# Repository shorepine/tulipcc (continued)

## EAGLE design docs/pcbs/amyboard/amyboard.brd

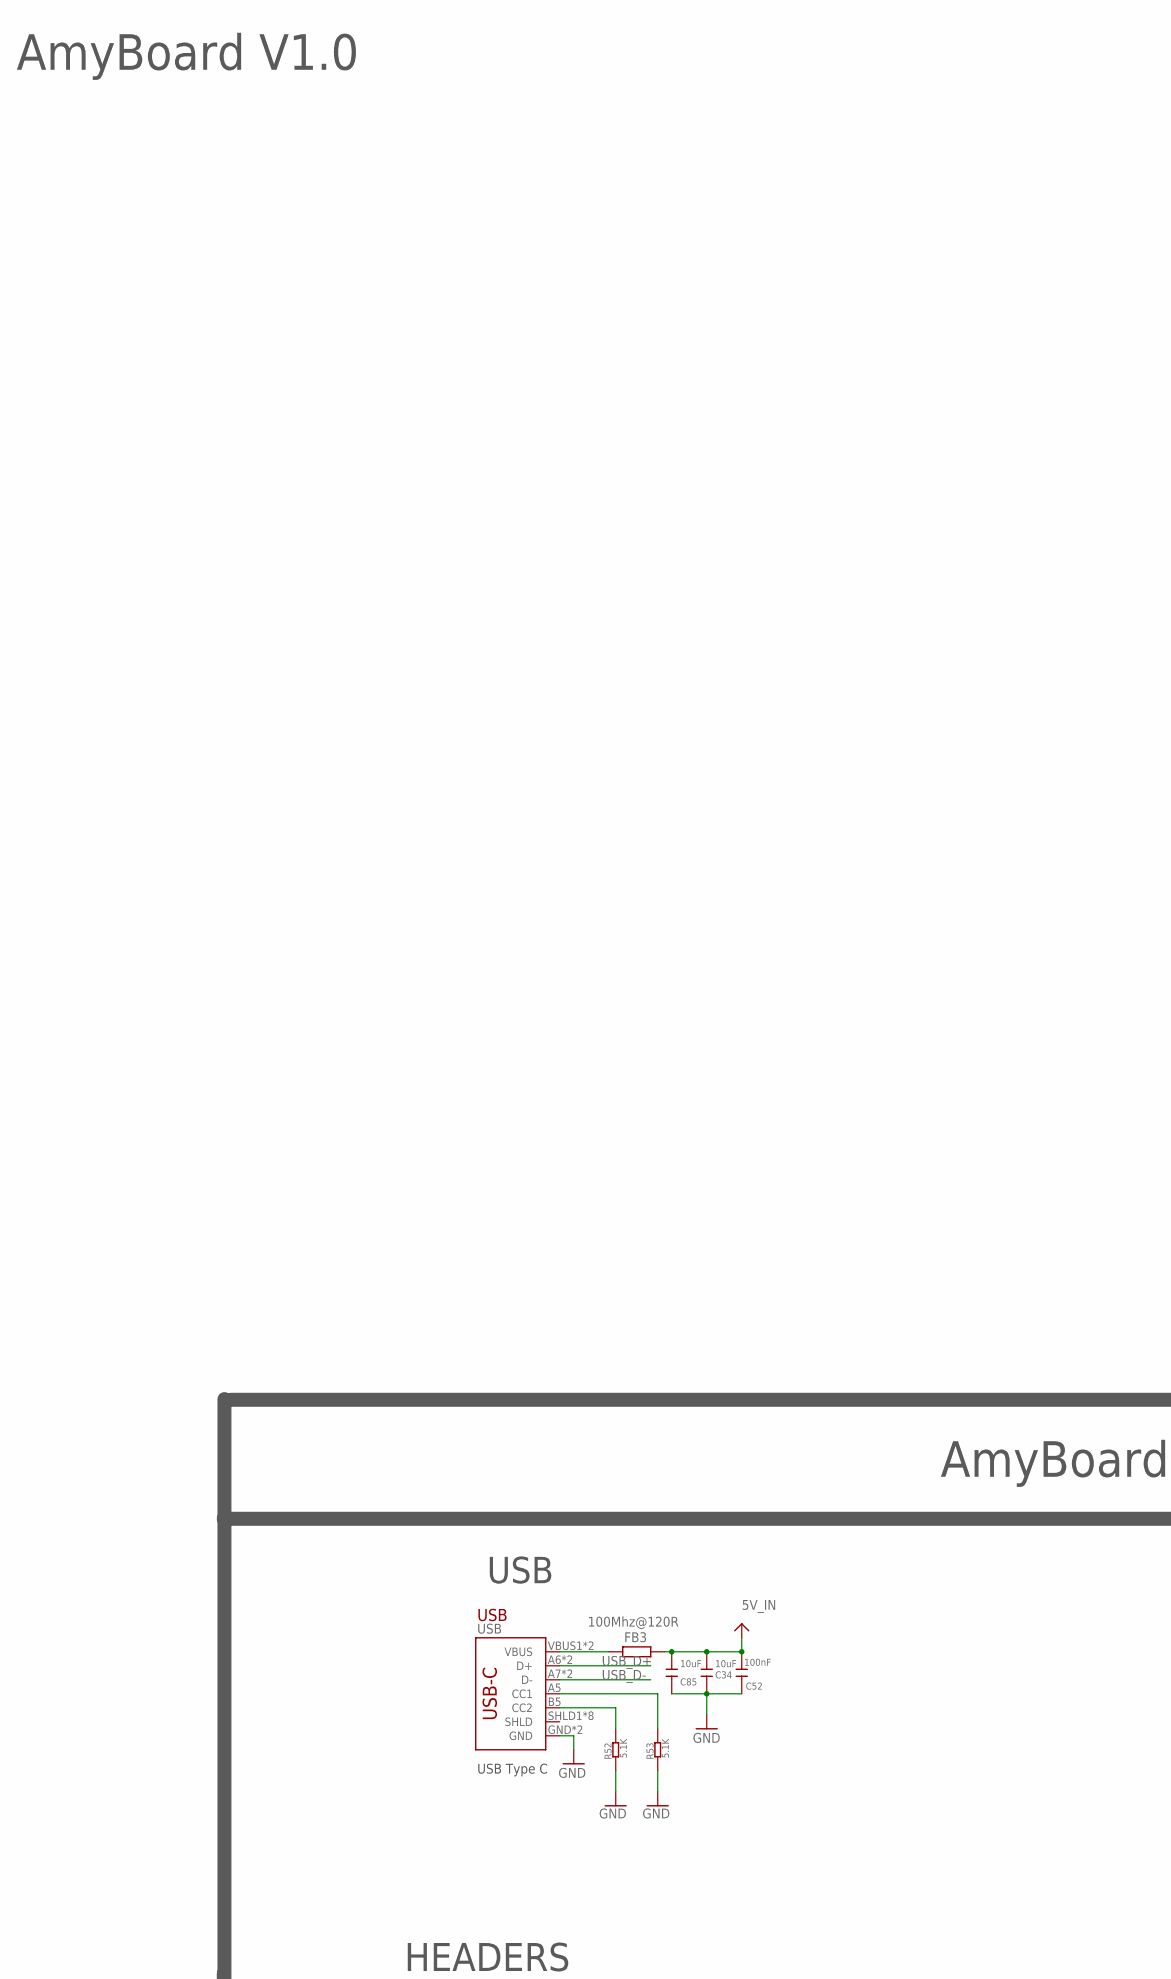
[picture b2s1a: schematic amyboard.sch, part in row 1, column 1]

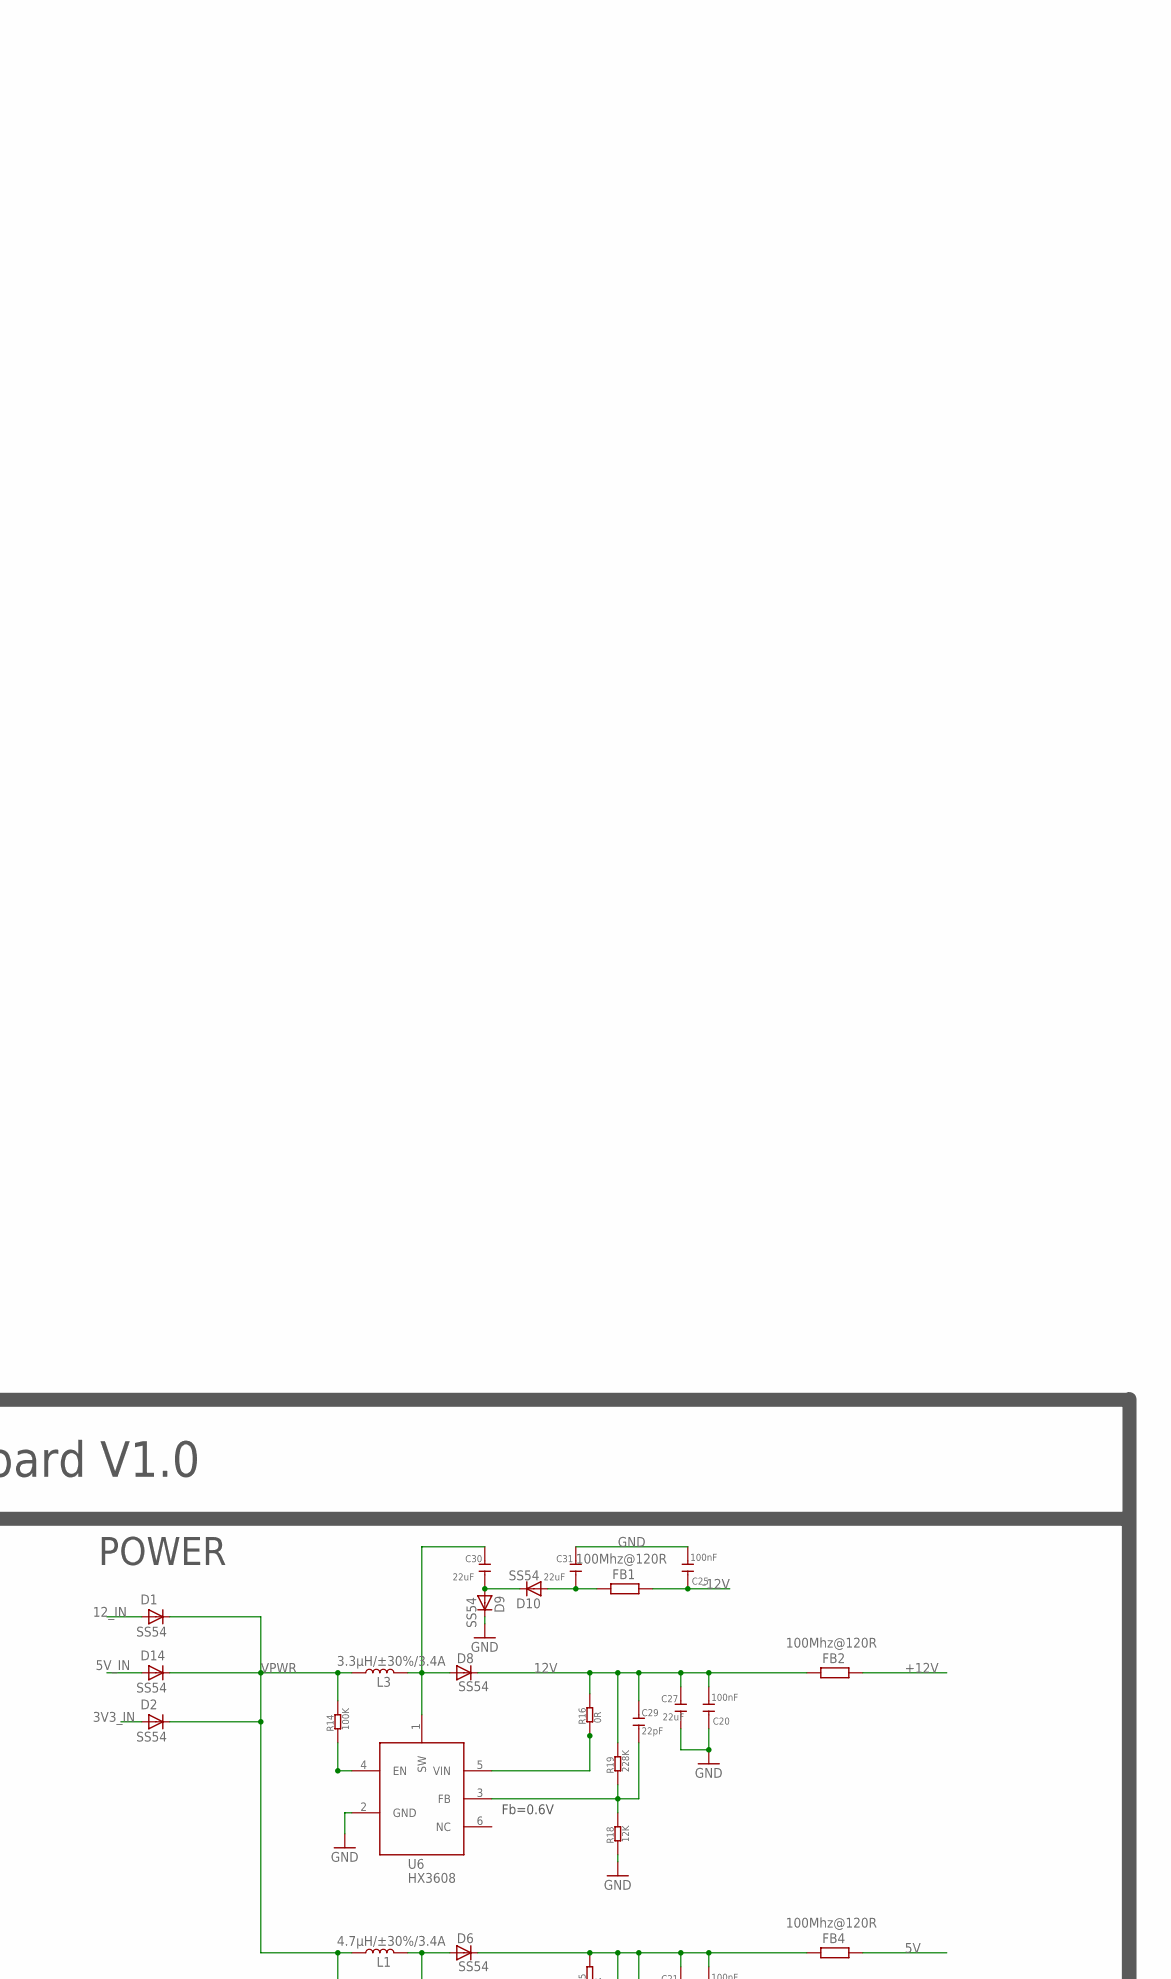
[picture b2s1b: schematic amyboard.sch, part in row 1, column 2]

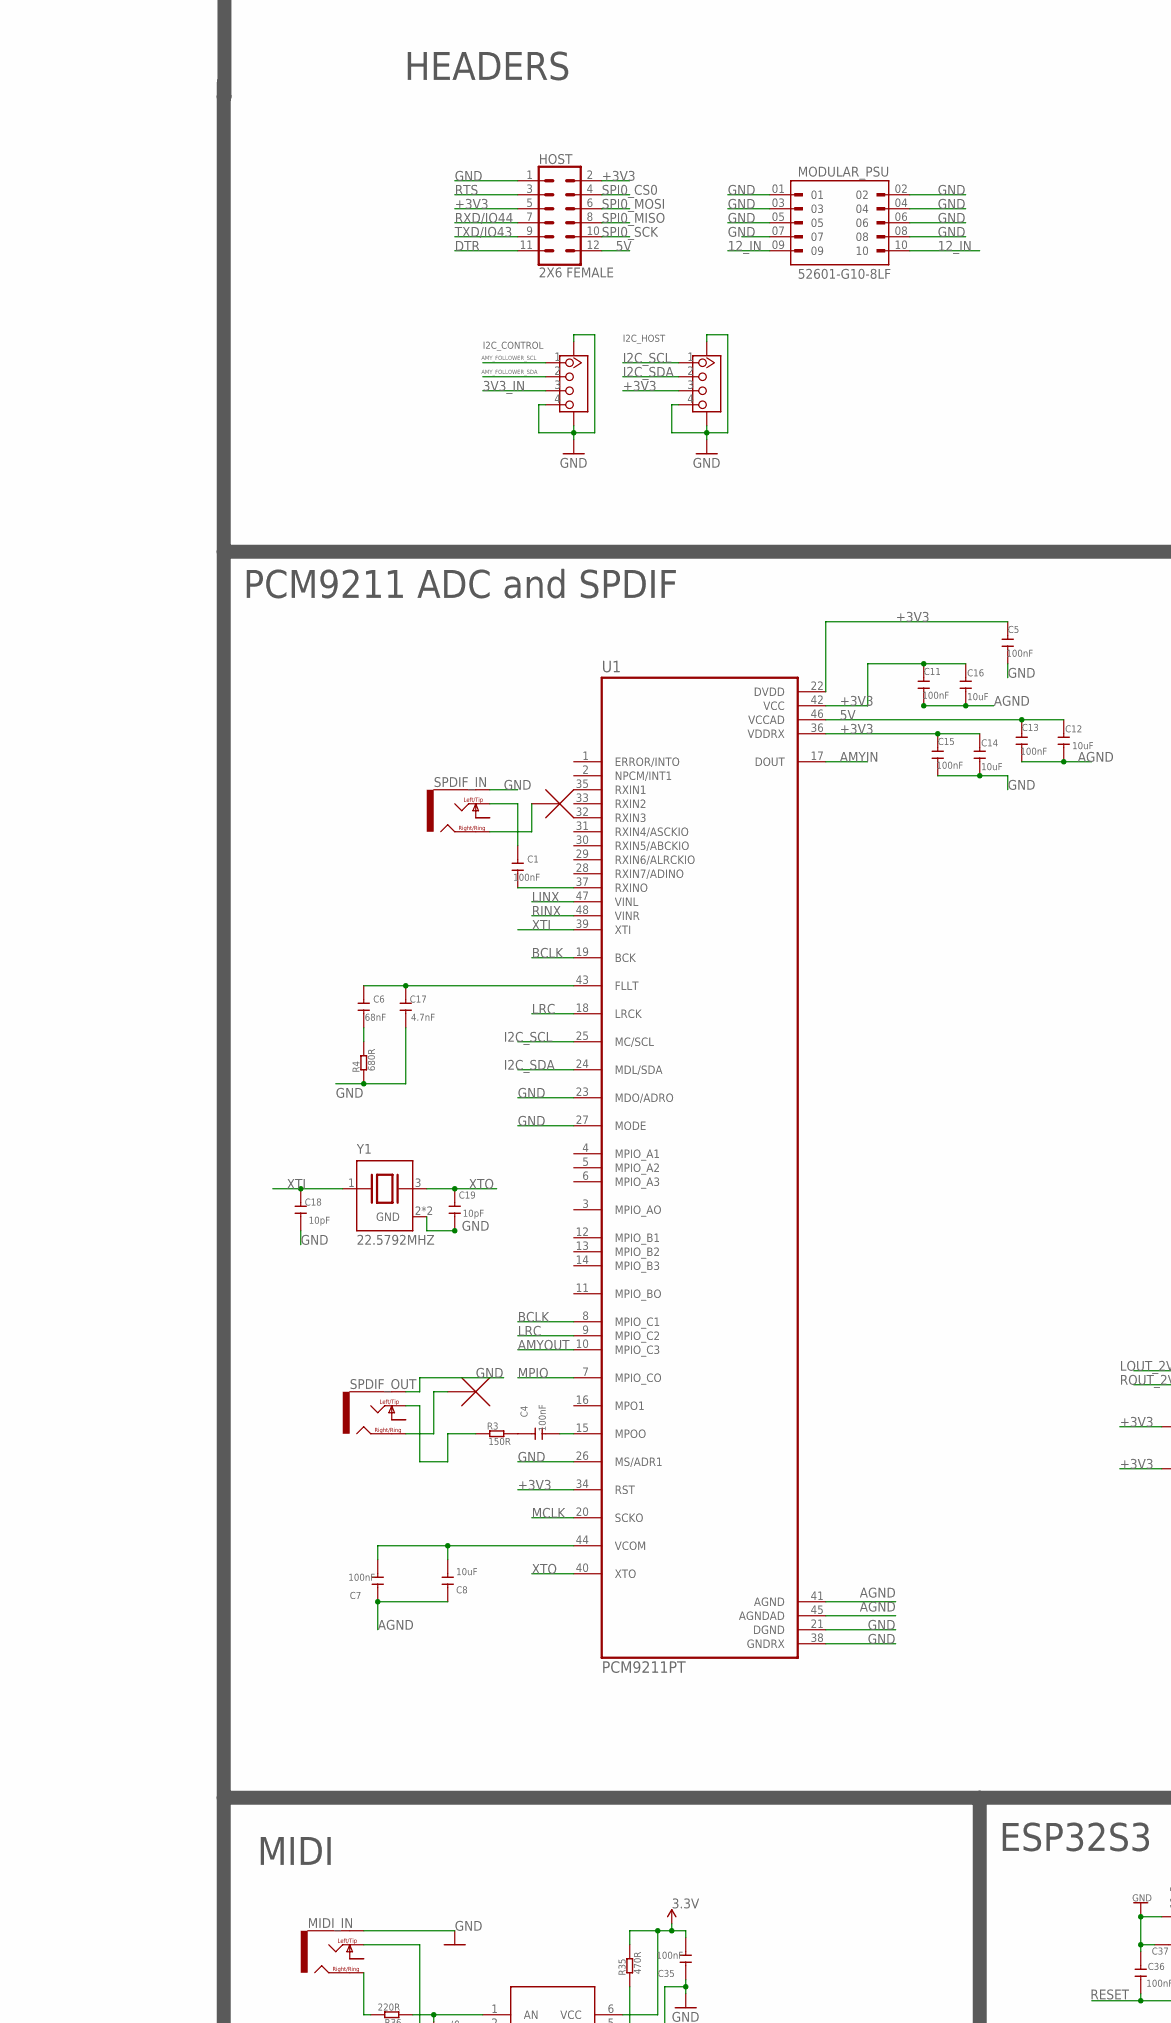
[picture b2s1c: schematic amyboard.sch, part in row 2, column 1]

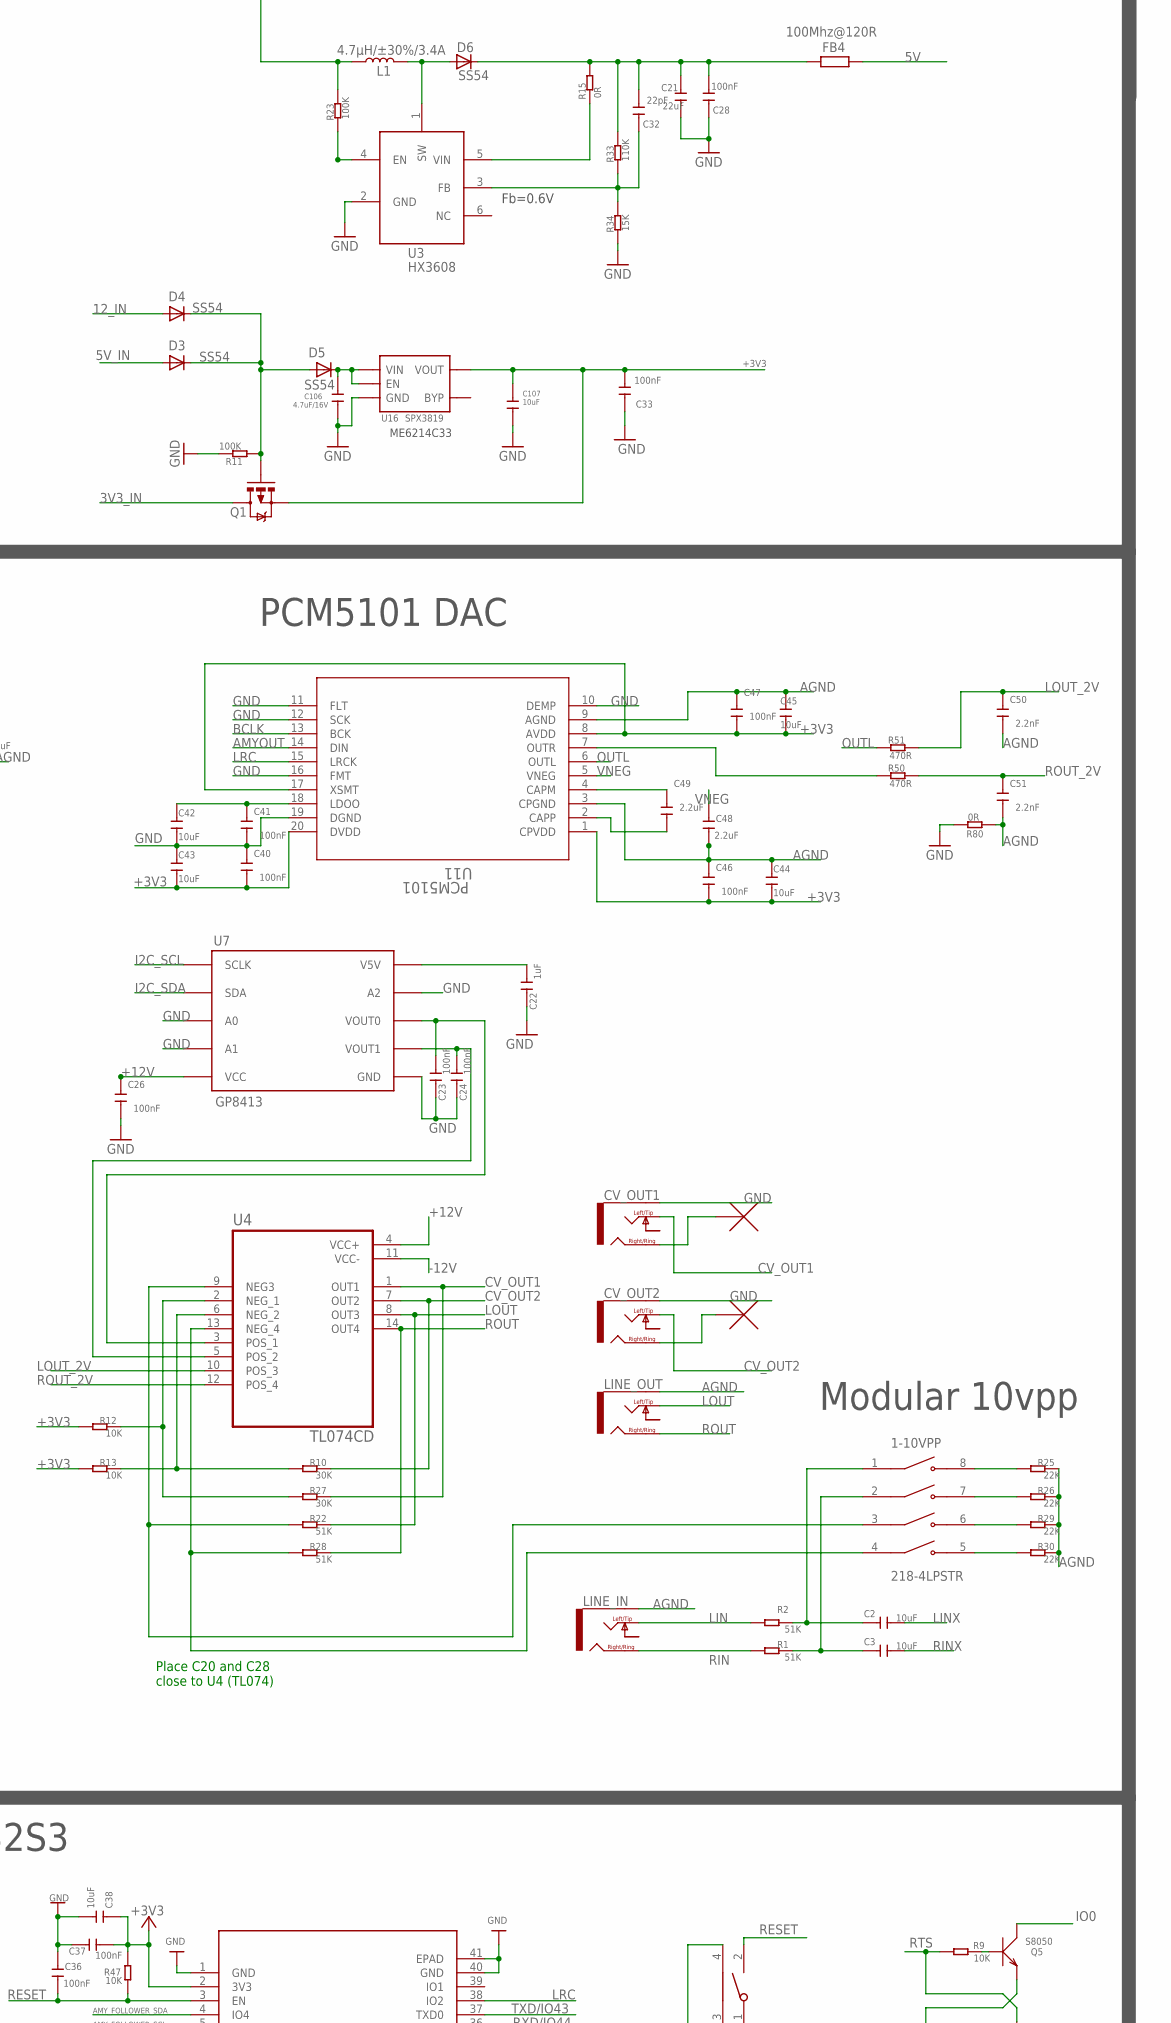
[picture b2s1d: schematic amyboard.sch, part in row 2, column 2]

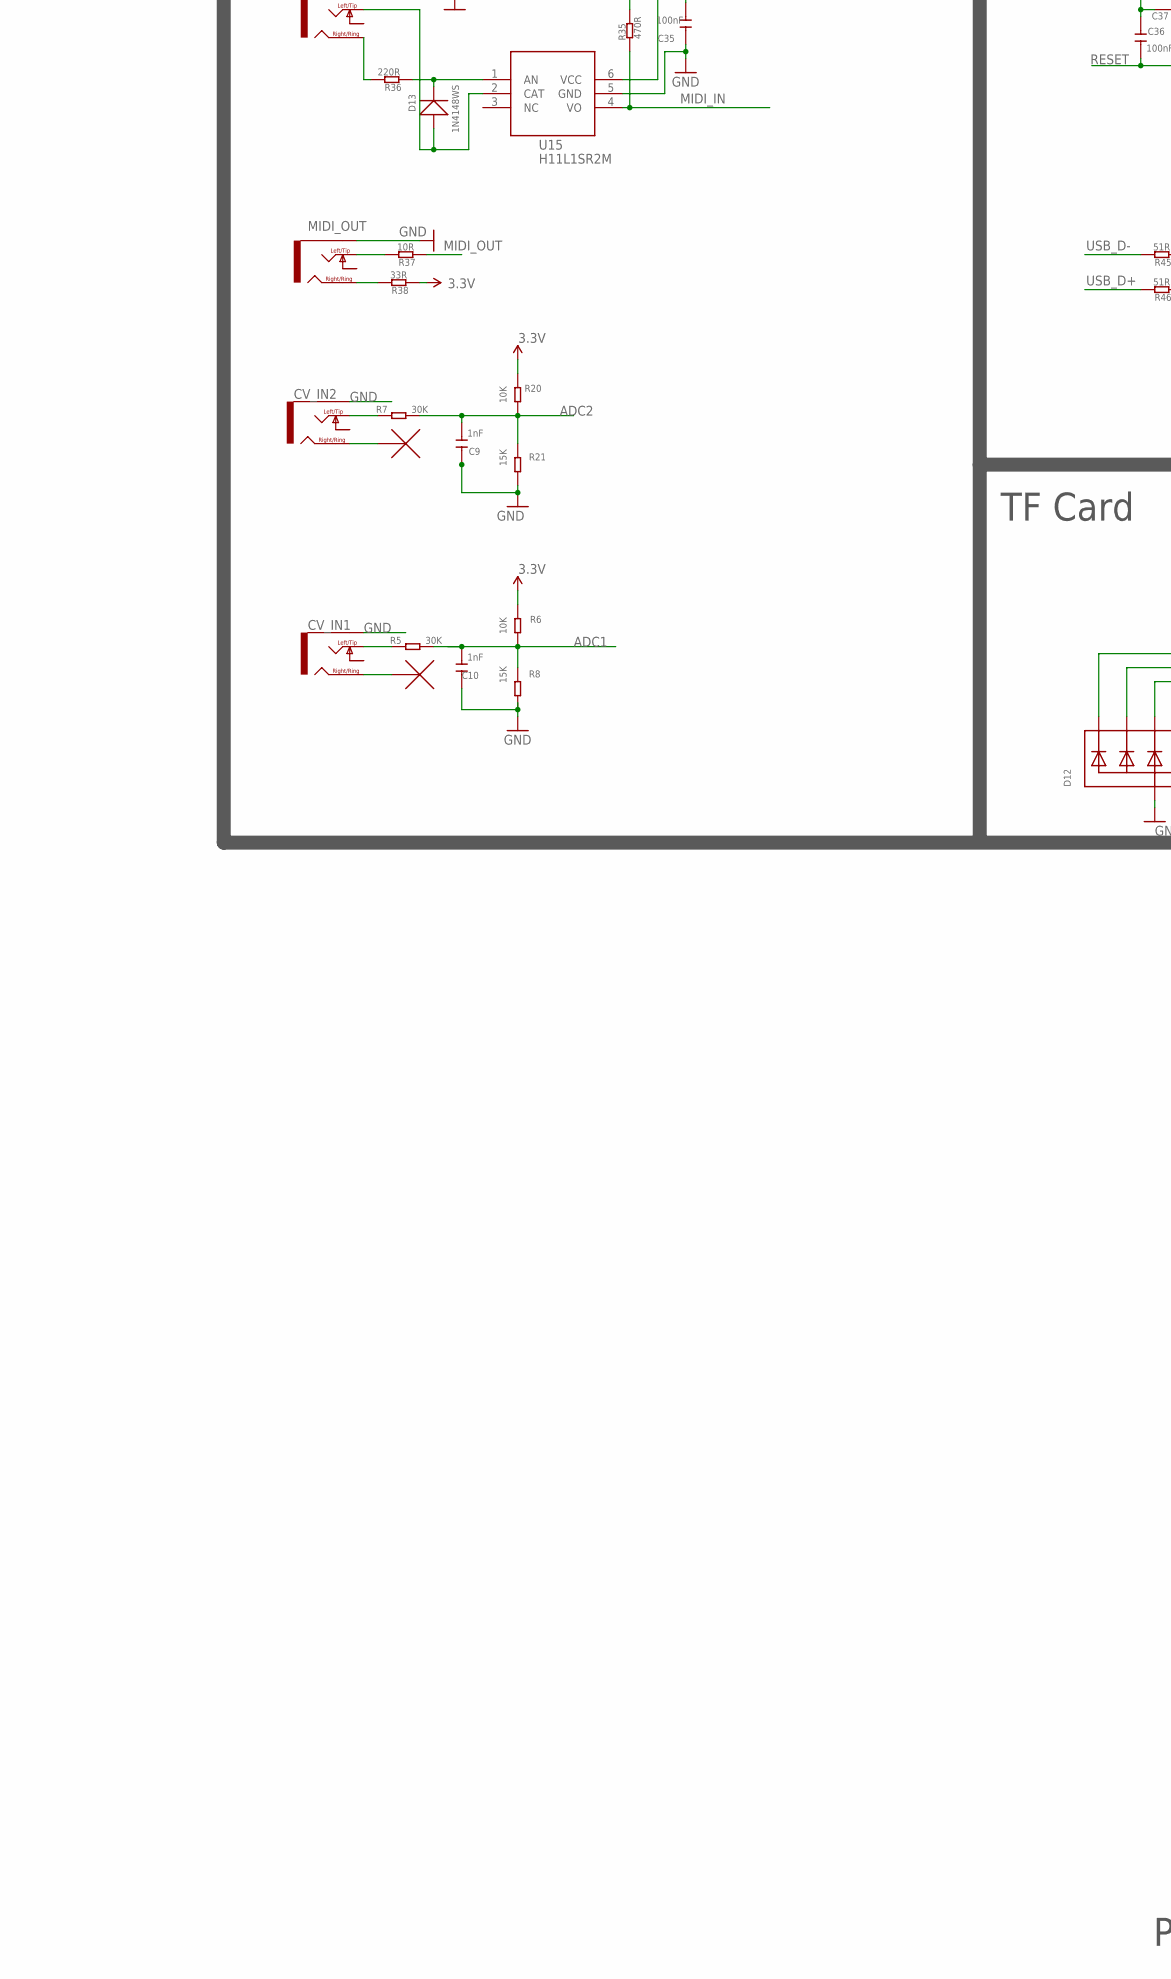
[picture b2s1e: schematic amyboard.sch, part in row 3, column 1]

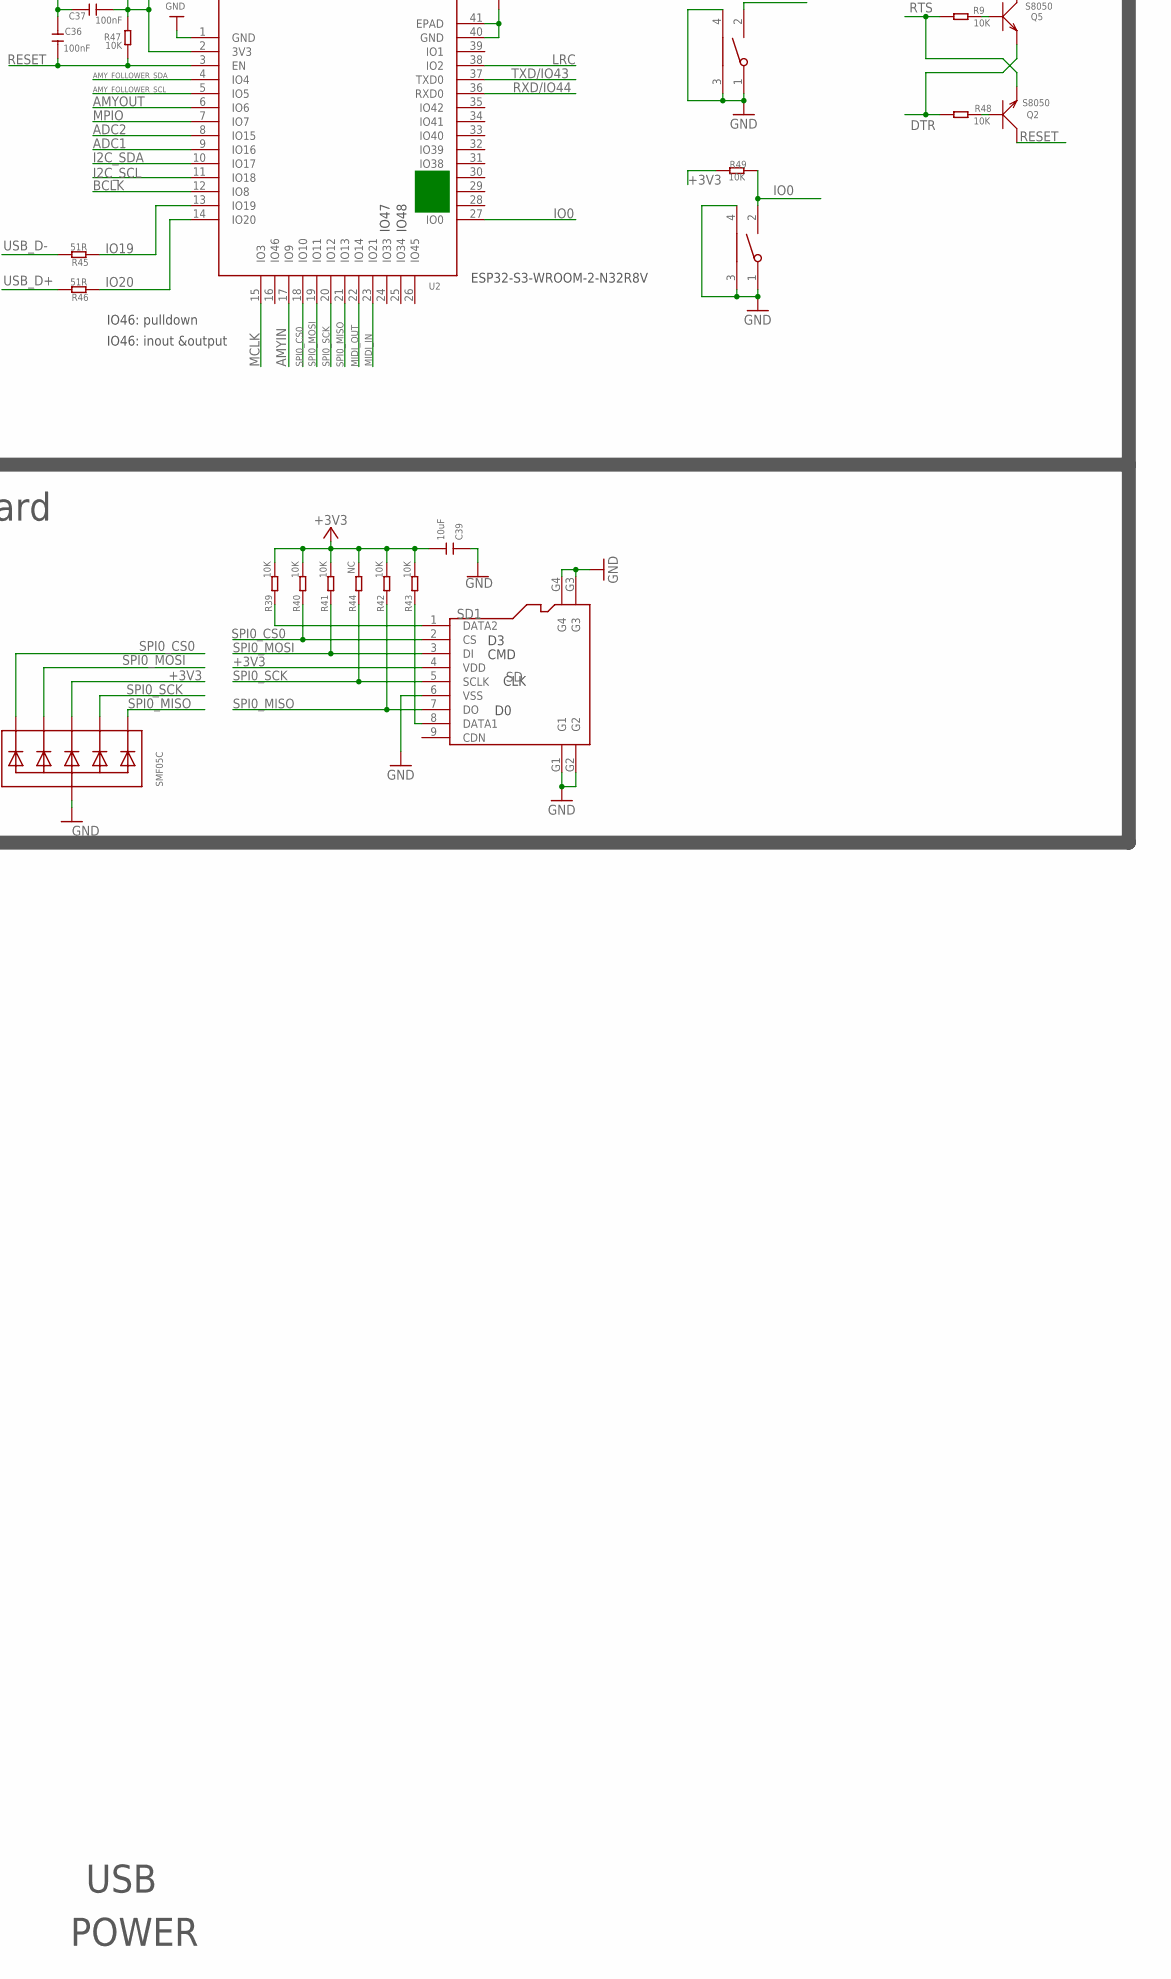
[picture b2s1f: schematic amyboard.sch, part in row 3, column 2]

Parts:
1-10VPP: 218-4LPSTR; SW_218-4LPSTR
BOOT: TS24CA; 2*4*3.5MM
C1, C4, C5, C7, C11, C13, C15, C20, C23, C24, C25, C26, C28, C33, C35, C36, C37, C40, C41, C46, C47, C52: 100nF; DISCRETE_C0402
C2, C3, C8, C12, C14, C16, C34, C38, C39, C42, C43, C44, C45, C85: 10uF; DISCRETE_C0603
C6: 68nF; DISCRETE_C0402
C9, C10: 1nF; DISCRETE_C0402
C17: 4.7nF; DISCRETE_C0402
C18, C19: 10pF; DISCRETE_C0402
C21, C27, C30, C31: 22uF; C0603
C22: 1uF; DISCRETE_C0402
C29: 22pF; C0603
C32: 22pF; DISCRETE_C0402
C48, C49: 2.2uF; DISCRETE_C0402
C50, C51: 2.2nF; DISCRETE_C0402
C106: 4.7uF/16V; 0603
C107: 10uF; 0603
CV_IN1, CV_IN2: NV-PJ3410_STEREO; NV-PJ3410_SOCKET
CV_OUT1, CV_OUT2: NV-PJ3410_STEREO; NV-PJ3410_SOCKET
D1, D2, D3, D4, D5, D6, D8, D9, D10, D14: SS54; DO-214AC
D12: SMF05C; SOT363
D13: 1N4148WS; SOD323
FB1, FB2, FB3, FB4: 100Mhz@120R; R0805
HOST: 2X6 FEMALE; 2X6
I2C_CONTROL, I2C_HOST: GROVE-CONNECTOR-SMD'90D'; HW4-SMD-2.0-90D
L1: 4.7µH/±30%/3.4A; CR54
L3: 3.3µH/±30%/3.4A; CR54
LINE_IN: NV-PJ3410_STEREO; NV-PJ3410_SOCKET
LINE_OUT: NV-PJ3410_STEREO; NV-PJ3410_SOCKET
MIDI_IN: NV-PJ3410_STEREO; NV-PJ3410_SOCKET
MIDI_OUT: NV-PJ3410_STEREO; NV-PJ3410_SOCKET
MODULAR_PSU: 52601-G10-8LF; AMPHENOL_52601-G10-8LF
PCM5101: U11; PW20_TEX
Q1: AO3407; SOT23-3
Q2, Q5: S8050; SOT23
R1, R2, R22, R28: 51K; DISCRETE_R0402
R3: 150R; DISCRETE_R0402
R4: 680R; DISCRETE_R0402
R5, R7, R10, R27: 30K; DISCRETE_R0402
R6, R9, R12, R13, R20, R39, R40, R41, R42, R43, R47, R48, R49: 10K; DISCRETE_R0402
R8, R21, R34: 15K; DISCRETE_R0402
R11, R14, R23: 100K; DISCRETE_R0402
R15, R16: 0R; DISCRETE_R0402
R18: 12K; DISCRETE_R0402
R19: 228K; DISCRETE_R0402
R25, R26, R29, R30: 22K; DISCRETE_R0402
R33: 110K; DISCRETE_R0402
R35, R50, R51: 470R; DISCRETE_R0402
R36: 220R; DISCRETE_R0402
R37: 10R; DISCRETE_R0402
R38: 33R; DISCRETE_R0402
R44: NC; DISCRETE_R0402
R45, R46: 51R; DISCRETE_R0402
R52, R53: 5.1K; DISCRETE_R0402
R80: 0R; DISCRETE_R0603
RST: TS24CA; 2*4*3.5MM
SD1: SD; 9P-SMD-W/-RING
SPDIF_IN: NV-PJ3410_STEREO; NV-PJ3410_SOCKET
SPDIF_OUT: NV-PJ3410_STEREO; NV-PJ3410_SOCKET
U1: PCM9211PT; QFP50P900X900X160-48N
U2: ESP32­S2­SOLO; ESP32-­S2-­SOLO
U3, U6: HX3608; SOT-23-6
U4: TL074CD; SOIC127P600X175-14N
U7: GP8413; SOIC-10
U15: H11L1SR2M; SOP-6-2.54MM
U16: SPX3819; SOT23-5
USB: USB-C; USB-C-16P-5
Y1: 22.5792MHZ; XTAL_ABM10W-22.5792MHZ-8-K1Z-T3

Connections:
3.3V: C35.1, R6.2, R20.2, R35.1, R38.2, U15.6 (VCC)
3V3_IN: D2.A, I2C_CONTROL.3, Q1.3 (D)
5V: C12.2, C13.1, FB4.2, HOST.12, U1.46 (VCCAD)
5V_IN: C34.2, C52.2, C85.2, D3.A, D14.A, FB3.2
12V: C20.2, C21.1, C27.1, C28.2, C29.1, C32.2, D6.C, D8.C, FB2.1, FB4.1, R15.1, R16.1, R19.1, R33.1
12_IN: D1.A, D4.A, MODULAR_PSU.09, MODULAR_PSU.10
+3V3: C5.1, C11.1, C14.2, C15.1, C16.2, C33.2, C37.2, C38.1, C39.2, C40.1, C43.1, C44.1, C45.1, C46.1, C47.1, C107.1, D12.4 (C3), HOST.2, HOST.5, I2C_HOST.3, PCM5101.1 (CPVDD), PCM5101.8 (AVDD), PCM5101.17 (XSMT), PCM5101.20 (DVDD), Q1.2 (S), R12.2, R13.2, R39.2, R40.2, R41.2, R42.2, R43.2, R44.2, R47.2, R49.2, SD1.4 (VDD), U1.22 (DVDD), U1.34 (RST), U1.36 (VDDRX), U1.42 (VCC), U2.2 (3V3), U16.5 (VOUT)
+12V: C26.2, FB2.2, U4.4 (VCC+), U7.5 (VCC)
-12V: C25.1, FB1.2, U4.11 (VCC-)
ADC1: C10.1, R5.1, R6.1, R8.2, U2.9 (IO16)
ADC2: C9.1, R7.1, R20.1, R21.2, U2.8 (IO15)
AGND: C7.2, C8.1, C11.2, C12.1, C13.2, C16.1, C44.2, C45.2, C46.2, C47.2, C48.1, C50.1, C51.1, LINE_IN.GND (EARTH), LINE_OUT.GND (EARTH), PCM5101.3 (CPGND), PCM5101.9 (AGND), R25.1, R26.1, R29.1, R30.1, R80.1, U1.41 (AGND), U1.45 (AGNDAD)
AMYIN: U1.17 (DOUT), U2.17 (IO9)
AMYOUT: PCM5101.14 (DIN), U1.10 (MPIO_C3), U2.6 (IO6)
AMY_FOLLOWER_SCL: I2C_CONTROL.1, U2.5 (IO5)
AMY_FOLLOWER_SDA: I2C_CONTROL.2, U2.4 (IO4)
BCLK: PCM5101.13 (BCK), U1.8 (MPIO_C1), U1.19 (BCK), U2.12 (IO8)
CV_OUT1: CV_OUT1.LEFT/TIP (TIP), R27.1, U4.1 (OUT1)
CV_OUT2: CV_OUT2.LEFT/TIP (TIP), R10.1, U4.7 (OUT2)
DTR: HOST.11, Q5.2 (E), R48.2
ENABLE: R14.2, U6.4 (EN)
ENABLE1: R23.2, U3.4 (EN)
GND: BOOT.1, BOOT.3, BOOT.4, C5.2, C9.2, C10.2, C14.1, C15.2, C17.1, C18.1, C19.1, C20.1, C21.2, C22.1, C23.1, C24.1, C25.2, C26.1, C27.2, C28.1, C31.1, C33.1, C34.1, C35.2, C36.1, C37.1, C38.2, C39.1, C40.2, C41.1, C42.1, C43.2, C52.1, C85.1, C106.2, C107.2, CV_IN1.GND (EARTH), CV_IN2.GND (EARTH), CV_OUT1.GND (EARTH), CV_OUT2.GND (EARTH), D9.C, D12.2 (A), HOST.1, I2C_CONTROL.4, I2C_CONTROL.SS1, I2C_CONTROL.SS2, I2C_HOST.4, I2C_HOST.SS1, I2C_HOST.SS2, MIDI_IN.GND (EARTH), MIDI_OUT.GND (EARTH), MODULAR_PSU.01, MODULAR_PSU.02, MODULAR_PSU.03, MODULAR_PSU.04, MODULAR_PSU.05, MODULAR_PSU.06, MODULAR_PSU.07, MODULAR_PSU.08, PCM5101.10 (DEMP), PCM5101.11 (FLT), PCM5101.12 (SCK), PCM5101.16 (FMT), PCM5101.19 (DGND), R4.2, R8.1, R11.1, R18.2, R21.1, R34.2, R52.2, R53.2, R80.2, RST.1, RST.3, RST.4, SD1.6 (VSS), SD1.G1, SD1.G2, SD1.G3, SD1.G4, SPDIF_IN.GND (EARTH), SPDIF_OUT.GND (EARTH), U1.21 (DGND), U1.23 (MDO/ADRO), U1.26 (MS/ADR1), U1.27 (MODE), U1.38 (GNDRX), U2.1 (GND), U2.40 (GND), U2.41 (EPAD), U3.2 (GND), U6.2 (GND), U7.3 (A0), U7.4 (A1), U7.6 (GND), U7.9 (A2), U15.5 (GND), U16.2 (GND), USB.GND, USB.GND2 (GND), Y1.2 (GND), Y1.4 (GND)
I2C_SCL: I2C_HOST.1, U1.25 (MC/SCL), U2.11 (IO18), U7.1 (SCLK)
I2C_SDA: I2C_HOST.2, U1.24 (MDL/SDA), U2.10 (IO17), U7.2 (SDA)
IO0: BOOT.2, Q5.3 (C), R49.1, U2.27 (IO0)
IO19: R45.2, U2.13 (IO19)
IO20: R46.2, U2.14 (IO20)
LIN: LINE_IN.LEFT/TIP (TIP), R2.2
LINX: C2.1, U1.47 (VINL)
LOUT: LINE_OUT.LEFT/TIP (TIP), R22.1, U4.8 (OUT3)
LOUT_2V: C50.2, R51.1, U4.10 (POS_3)
LRC: PCM5101.15 (LRCK), U1.9 (MPIO_C2), U1.18 (LRCK), U2.38 (IO2)
MCLK: U1.20 (SCKO), U2.15 (IO3)
MIDI_IN: R35.2, U2.23 (IO21), U15.4 (VO)
MIDI_OUT: R37.2, U2.22 (IO14)
MPIO: U1.7 (MPIO_CO), U2.7 (IO7)
unnamed: C1.1, U1.37 (RXINO)
unnamed: C4.2, R3.1
unnamed: C4.1, U1.15 (MPOO)
unnamed: 1-10VPP.1, C2.2, R2.1
unnamed: 1-10VPP.2, C3.2, R1.1
unnamed: C7.1, C8.2, U1.44 (VCOM)
unnamed: C6.2, C17.2, U1.43 (FLLT)
unnamed: C6.1, R4.1
unnamed: CV_IN2.LEFT/TIP (TIP), R7.2
unnamed: D6.A, L1.P$2 (2), U3.1 (SW)
unnamed: C31.2, D10.A, FB1.1
unnamed: C23.2, U4.3 (POS_1), U7.8 (VOUT0)
unnamed: CV_IN1.LEFT/TIP (TIP), R5.2
unnamed: C24.2, U4.5 (POS_2), U7.7 (VOUT1)
unnamed: C30.1, D8.A, L3.P$2 (2), U6.1 (SW)
unnamed: C22.2, U7.10 (V5V)
unnamed: D3.C, D4.C, D5.A, Q1.1 (G), R11.2
unnamed: C106.1, D5.C, U16.1 (VIN), U16.3 (EN)
unnamed: C32.1, R33.2, R34.1, U3.3 (FB)
unnamed: C29.2, R18.1, R19.2, U6.3 (FB)
unnamed: R16.2, U6.5 (VIN)
unnamed: C30.2, D9.A, D10.C
unnamed: R10.2, R13.1, U4.6 (NEG_2)
unnamed: R15.2, U3.5 (VIN)
unnamed: R12.1, R27.2, U4.2 (NEG_1)
unnamed: Q2.1 (B), R48.1
unnamed: 1-10VPP.5, R30.2
unnamed: 1-10VPP.6, R29.2
unnamed: Q5.1 (B), R9.1
unnamed: R53.1, USB.A5 (CC1)
unnamed: R52.1, USB.B5 (CC2)
unnamed: 1-10VPP.8, R25.2
unnamed: 1-10VPP.7, R26.2
unnamed: FB3.1, USB.VBUS1 (VBUS), USB.VBUS2 (VBUS)
unnamed: 1-10VPP.3, R22.2, U4.9 (NEG3)
unnamed: 1-10VPP.4, R28.2, U4.13 (NEG_4)
unnamed: C41.2, C42.2, PCM5101.18 (LDOO)
unnamed: PCM5101.7 (OUTR), R50.2
unnamed: C49.2, PCM5101.4 (CAPM)
unnamed: C49.1, PCM5101.2 (CAPP)
unnamed: D13.+, MIDI_IN.LEFT/TIP (TIP), U15.2 (CAT)
unnamed: MIDI_IN.RIGHT/RING (RING), R36.1
unnamed: D13.-, R36.2, U15.1 (AN)
unnamed: MIDI_OUT.LEFT/TIP (TIP), R37.1
unnamed: MIDI_OUT.RIGHT/RING (RING), R38.1
unnamed: R39.1, SD1.1 (DATA2)
unnamed: R43.1, SD1.8 (DATA1)
OUTL: PCM5101.6 (OUTL), R51.2
RESET: C36.2, Q2.3 (C), R47.1, RST.2, U2.3 (EN)
RIN: LINE_IN.RIGHT/RING (RING), R1.2
RINX: C3.1, U1.48 (VINR)
ROUT: LINE_OUT.RIGHT/RING (RING), R28.1, U4.14 (OUT4)
ROUT_2V: C51.2, R50.1, U4.12 (POS_4)
RTS: HOST.3, Q2.2 (E), R9.2
RXD/IO44: HOST.7, U2.36 (RXD0)
SPDIFIN_SIGNAL: C1.2, SPDIF_IN.LEFT/TIP (TIP)
SPDIFOUT_SIGNAL: R3.2, SPDIF_OUT.LEFT/TIP (TIP)
SPI0_CS0: D12.1 (C1), HOST.4, R40.1, SD1.2 (CS), U2.18 (IO10)
SPI0_MISO: D12.6 (C5), HOST.8, R42.1, SD1.7 (DO), U2.21 (IO13)
SPI0_MOSI: D12.3 (C2), HOST.6, R41.1, SD1.3 (DI), U2.19 (IO11)
SPI0_SCK: D12.5 (C4), HOST.10, R44.1, SD1.5 (SCLK), U2.20 (IO12)
TXD/IO43: HOST.9, U2.37 (TXD0)
USB_D+: R46.1, USB.A6 (D+), USB.B6 (D+)
USB_D-: R45.1, USB.A7 (D-), USB.B7 (D-)
VNEG: C48.2, PCM5101.5 (VNEG)
VPWR: D1.C, D2.C, D14.C, L1.P$1 (1), L3.P$1 (1), R14.1, R23.1
XTI: C18.2, U1.39 (XTI), Y1.1
XTO: C19.2, U1.40 (XTO), Y1.3 (2)

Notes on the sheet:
USB
USB Type C
IO46: pulldown
IO46: inout &output
ESP32-S3-WROOM-2-N32R8V
IO47
IO48
POWER
ME6214C33
MIDI
PCM9211 ADC and SPDIF
ESP32S3
HEADERS
TF Card
CMD
CLK
Modular 10vpp
Fb=0.6V
PCM5101 DAC
Place C20 and C28 close to U4 (TL074)
AmyBoard V1.0

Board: 2 copper layers, 155 parts (11 on the bottom side), 105 nets, no tracks yet.
